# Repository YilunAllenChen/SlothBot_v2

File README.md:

# SlothBot_v2.0
The SlothBot project, v2.0. Since 2020.

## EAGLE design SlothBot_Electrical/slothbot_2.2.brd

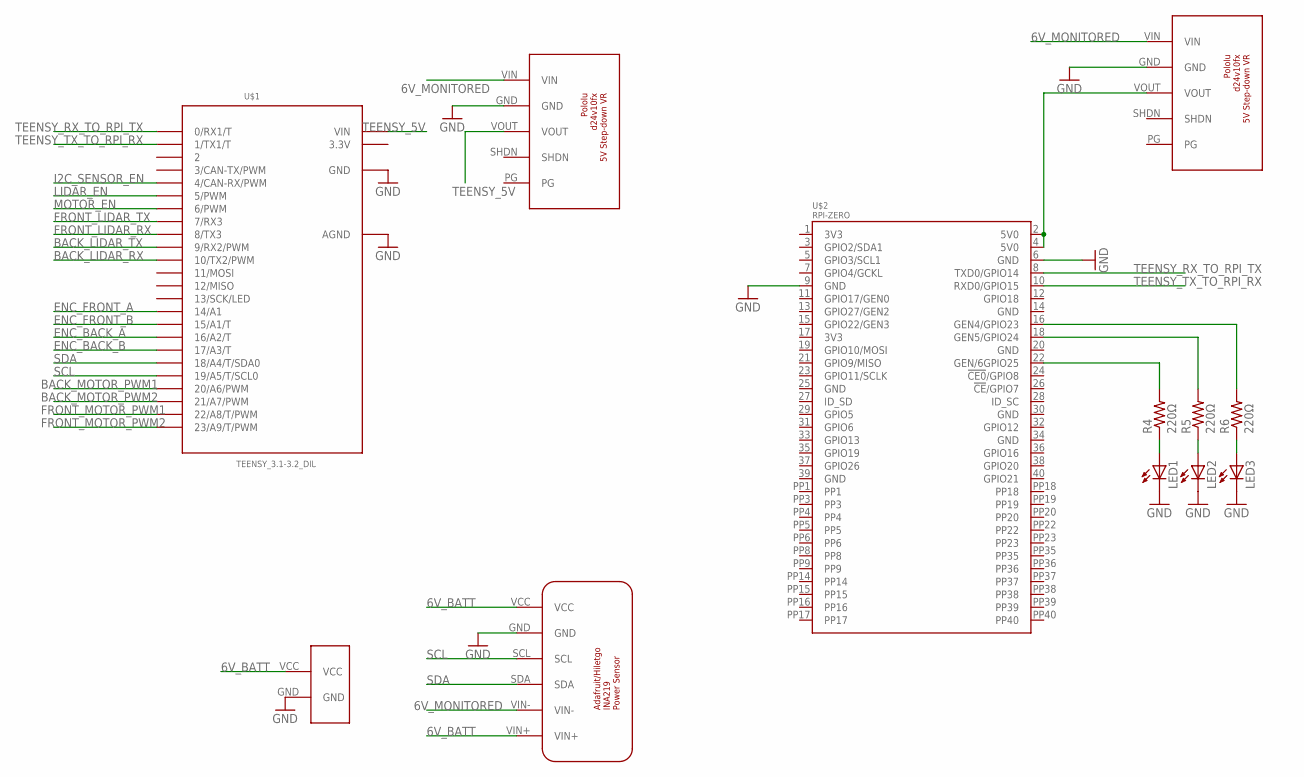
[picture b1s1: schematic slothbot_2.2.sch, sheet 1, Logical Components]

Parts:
LED1, LED2, LED3: LEDCHIPLED_0603; CHIPLED_0603
R4, R5, R6: 220Ω; R3216
U$1: TEENSY_3.1-3.2_DIL; TEENSY_3.0-3.2&LC_DIL
U$2: RPI-ZERO; RASP_PI_ZERO_BOARD_FULL
U$12, U$13: D24V10FX
U$15: INA219
U$16: BATTERY_CONNECTOR

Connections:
3.3V: U$1.3.3V
5V0@1: U$2.2 (5V0), U$2.4 (5V0), U$13.VOUT
6V_BATT: U$15.VCC, U$15.VIN+, U$16.VCC
6V_MONITORED: U$12.VIN, U$13.VIN, U$15.VIN-; also elsewhere on the board
BACK_LIDAR_RX: U$1.10 (10/TX2/PWM); also elsewhere on the board
BACK_LIDAR_TX: U$1.9 (9/RX2/PWM); also elsewhere on the board
BACK_MOTOR_PWM1: U$1.20/A6 (20/A6/PWM); also elsewhere on the board
BACK_MOTOR_PWM2: U$1.21/A7 (21/A7/PWM); also elsewhere on the board
ENC_BACK_A: U$1.16/A2 (16/A2/T); also elsewhere on the board
ENC_BACK_B: U$1.17/A3 (17/A3/T); also elsewhere on the board
ENC_FRONT_A: U$1.14/A0 (14/A1); also elsewhere on the board
ENC_FRONT_B: U$1.15/A1 (15/A1/T); also elsewhere on the board
FRONT_LIDAR_RX: U$1.8 (8/TX3); also elsewhere on the board
FRONT_LIDAR_TX: U$1.7 (7/RX3); also elsewhere on the board
FRONT_MOTOR_PWM1: U$1.22/A8 (22/A8/T/PWM); also elsewhere on the board
FRONT_MOTOR_PWM2: U$1.23/A9 (23/A9/T/PWM); also elsewhere on the board
GND: LED1.C, LED2.C, LED3.C, U$1.AGND, U$1.GND, U$2.6 (GND), U$12.GND, U$13.GND, U$15.GND, U$16.GND; also elsewhere on the board
GND@1: U$2.9 (GND)
I2C_SENSOR_EN: U$1.4 (4/CAN-RX/PWM); also elsewhere on the board
LIDAR_EN: U$1.5 (5/PWM); also elsewhere on the board
MOTOR_EN: U$1.6 (6/PWM); also elsewhere on the board
unnamed: LED1.A, R4.1
unnamed: LED2.A, R5.1
unnamed: LED3.A, R6.1
unnamed: R6.2, U$2.16 (GEN4/GPIO23)
unnamed: R5.2, U$2.18 (GEN5/GPIO24)
unnamed: R4.2, U$2.22 (GEN/6GPIO25)
SCL: U$1.19/A5 (19/A5/T/SCL0), U$15.SCL; also elsewhere on the board
SDA: U$1.18/A4 (18/A4/T/SDA0), U$15.SDA; also elsewhere on the board
TEENSY_5V: U$1.VIN, U$12.VOUT; also elsewhere on the board
TEENSY_RX_TO_RPI_TX: U$1.0 (0/RX1/T), U$2.8 (TXD0/GPIO14)
TEENSY_TX_TO_RPI_RX: U$1.1 (1/TX1/T), U$2.10 (RXD0/GPIO15)

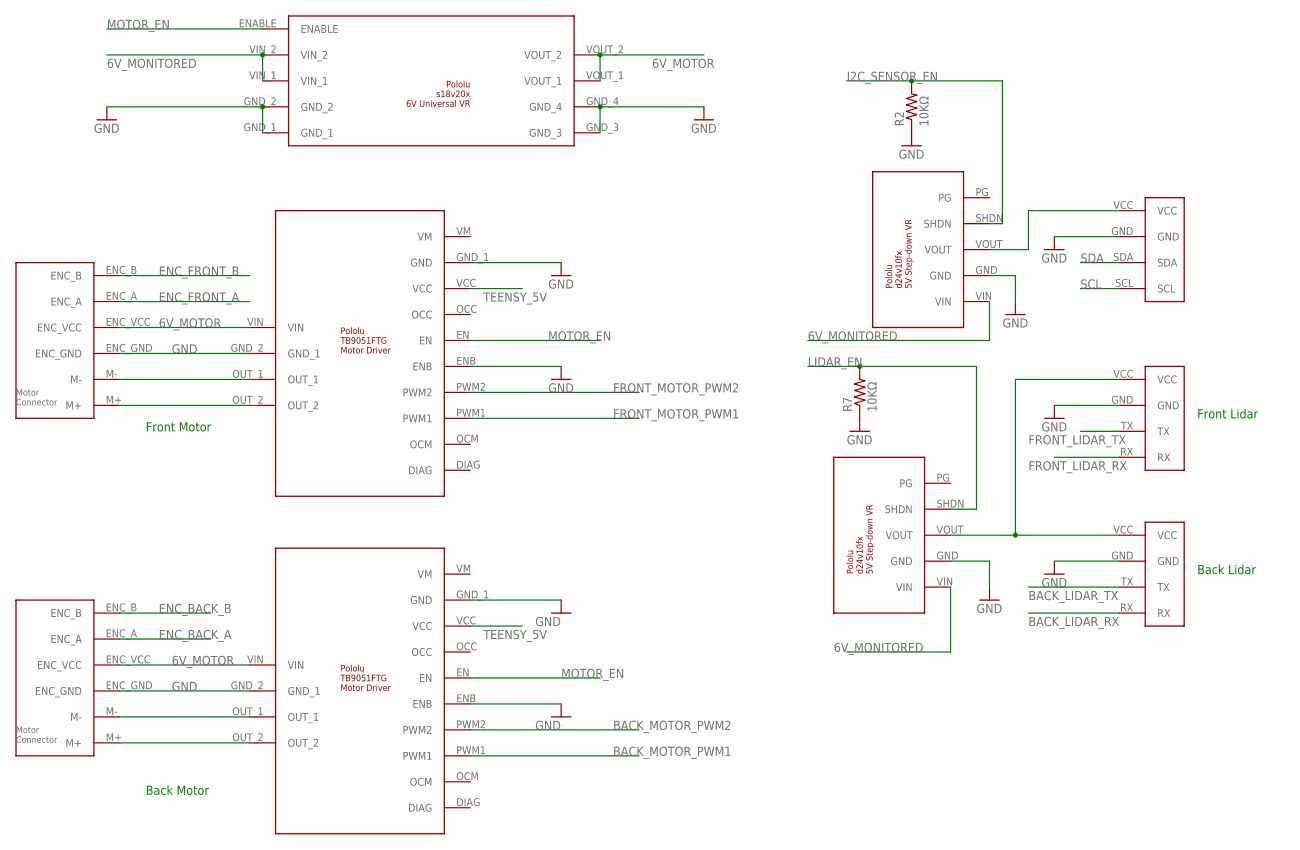
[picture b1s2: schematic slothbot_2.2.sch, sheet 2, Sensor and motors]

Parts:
R2, R7: 10KΩ; R3216
U$3, U$14: D24V10FX
U$4, U$5: MOTOR_CONNECTOR
U$6, U$7: SERIAL_CONNECTOR
U$8: I2C_CONNECTOR
U$9, U$10: TB9051FTG
U$11: S18V20X; S18V20F6

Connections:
6V_MONITORED: U$3.VIN, U$11.VIN_1, U$11.VIN_2, U$14.VIN; also elsewhere on the board
6V_MOTOR: U$4.ENC_VCC, U$5.ENC_VCC, U$9.VIN, U$10.VIN, U$11.VOUT_1, U$11.VOUT_2
BACK_LIDAR_RX: U$6.RX; also elsewhere on the board
BACK_LIDAR_TX: U$6.TX; also elsewhere on the board
BACK_MOTOR_PWM1: U$10.PWM1; also elsewhere on the board
BACK_MOTOR_PWM2: U$10.PWM2; also elsewhere on the board
ENC_BACK_A: U$5.ENC_A; also elsewhere on the board
ENC_BACK_B: U$5.ENC_B; also elsewhere on the board
ENC_FRONT_A: U$4.ENC_A; also elsewhere on the board
ENC_FRONT_B: U$4.ENC_B; also elsewhere on the board
FRONT_LIDAR_RX: U$7.RX; also elsewhere on the board
FRONT_LIDAR_TX: U$7.TX; also elsewhere on the board
FRONT_MOTOR_PWM1: U$9.PWM1; also elsewhere on the board
FRONT_MOTOR_PWM2: U$9.PWM2; also elsewhere on the board
GND: R2.1, R7.1, U$3.GND, U$4.ENC_GND, U$5.ENC_GND, U$6.GND, U$7.GND, U$8.GND, U$9.ENB, U$9.GND_1 (GND), U$9.GND_2 (GND_1), U$10.ENB, U$10.GND_1 (GND), U$10.GND_2 (GND_1), U$11.GND_1, U$11.GND_2, U$11.GND_3, U$11.GND_4, U$14.GND; also elsewhere on the board
I2C_SENSOR_EN: R2.2, U$14.SHDN; also elsewhere on the board
LIDAR_EN: R7.2, U$3.SHDN; also elsewhere on the board
MOTOR_EN: U$9.EN, U$10.EN, U$11.ENABLE; also elsewhere on the board
unnamed: U$3.VOUT, U$6.VCC, U$7.VCC
unnamed: U$4.M-, U$9.OUT_1
unnamed: U$4.M+, U$9.OUT_2
unnamed: U$5.M-, U$10.OUT_1
unnamed: U$5.M+, U$10.OUT_2
unnamed: U$8.VCC, U$14.VOUT
SCL: U$8.SCL; also elsewhere on the board
SDA: U$8.SDA; also elsewhere on the board
TEENSY_5V: U$9.VCC, U$10.VCC; also elsewhere on the board

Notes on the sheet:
Front Motor
Back Motor
Front Lidar
Back Lidar

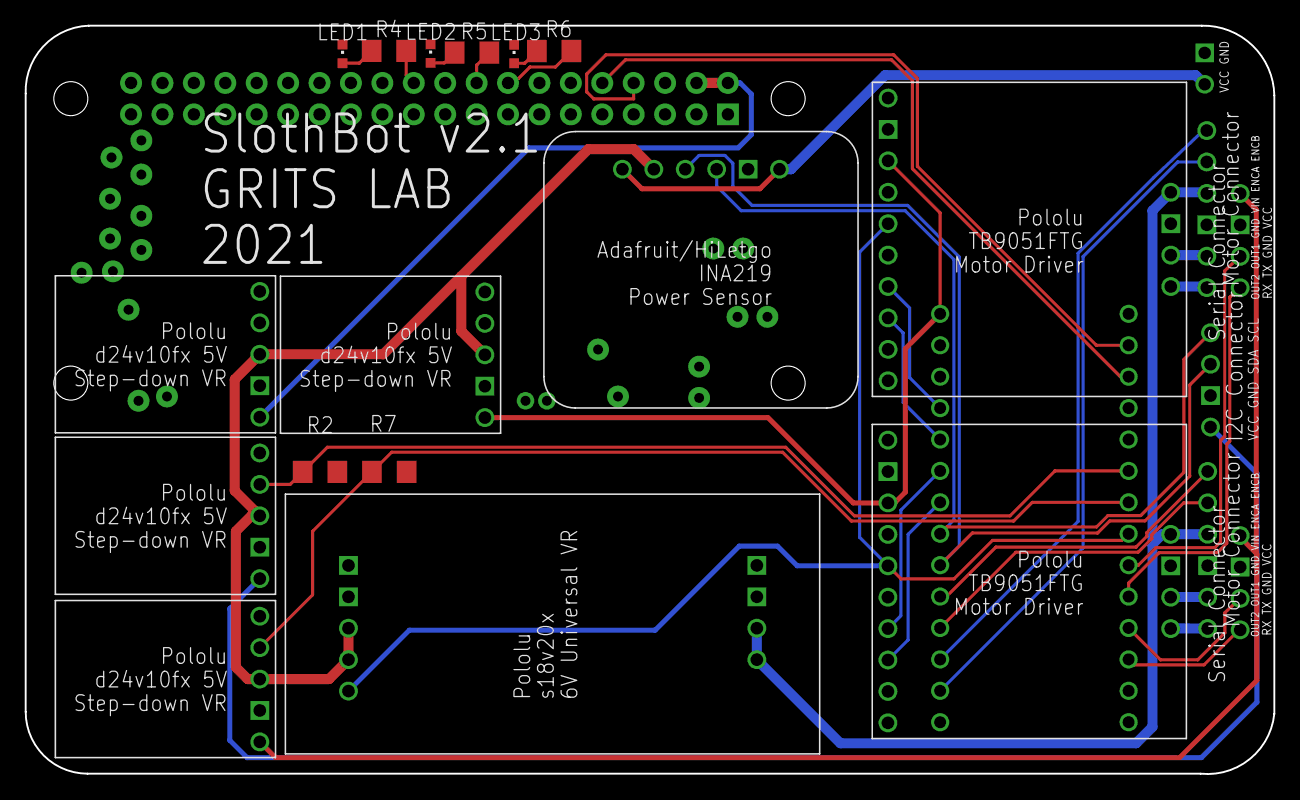
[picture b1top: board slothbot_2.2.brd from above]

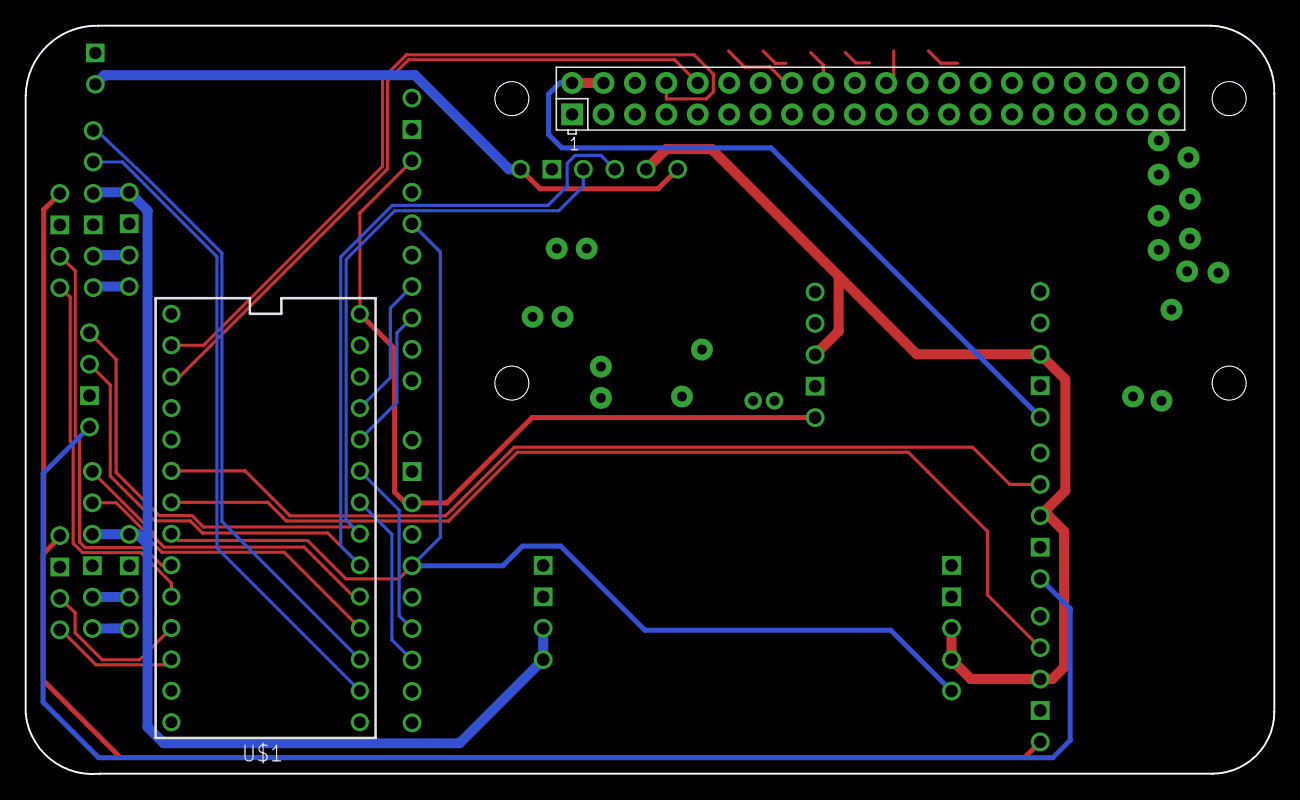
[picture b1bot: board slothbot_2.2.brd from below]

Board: 2 copper layers, 101.0 x 60.5 mm, 24 parts (2 on the bottom side), 37 nets.

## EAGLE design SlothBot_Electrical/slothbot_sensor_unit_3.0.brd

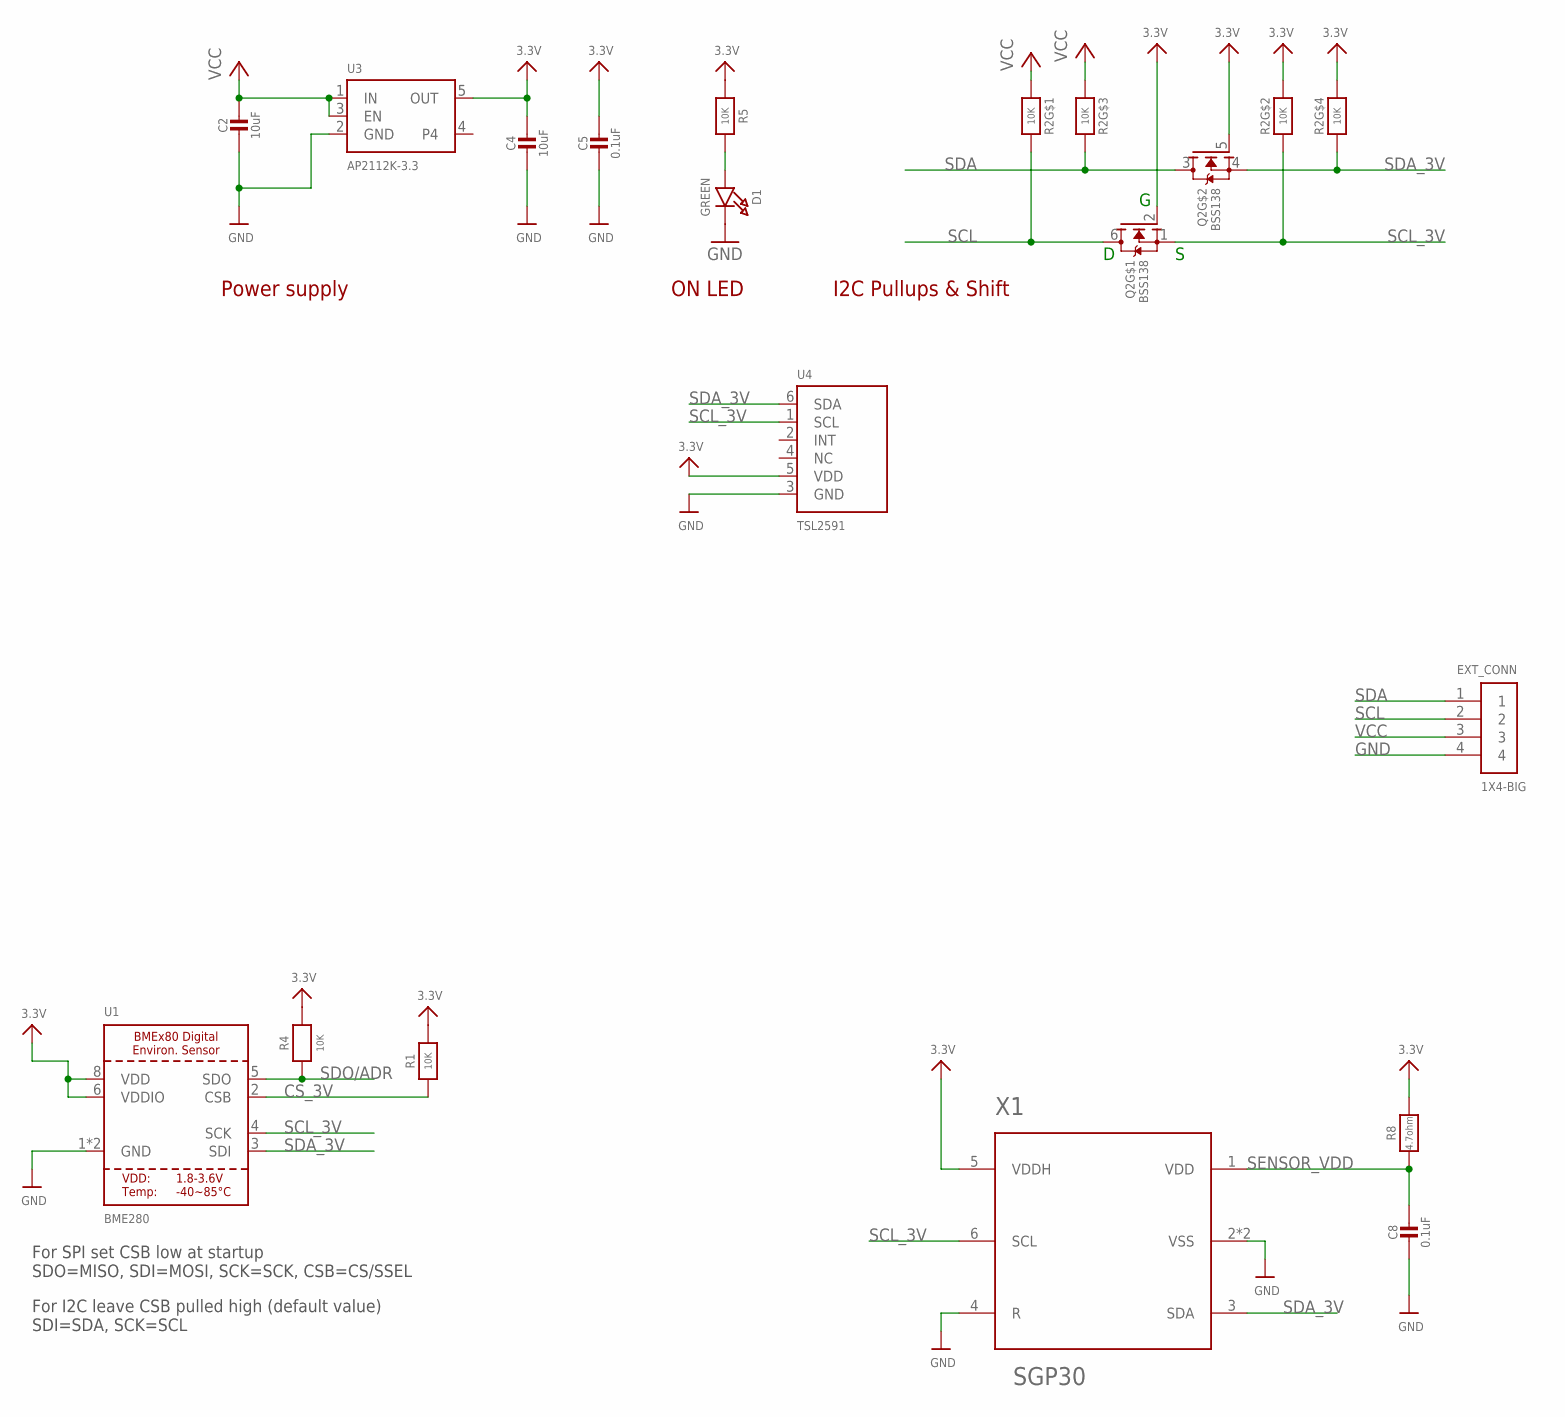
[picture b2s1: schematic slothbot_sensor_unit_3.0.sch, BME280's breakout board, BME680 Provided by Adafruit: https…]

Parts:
C2, C4: 10uF; 0805-NO
C5, C8: 0.1uF; 0603-NO
D1: GREEN; CHIPLED_0603_NOOUTLINE
EXT_CONN: 1X4-BIG; 1X04-BIG
Q2: BSS138; SOT363
R1, R4, R5: 10K; 0603-NO
R2: 10K; RESPACK_4X0603
R8: 4.7ohm; 0603-NO
U1: BME280
U3: AP2112K-3.3; SOT23-5
U4: TSL2591; DFN6_TAOS
X1: SGP30

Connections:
3.3V: C4.1, C5.1, Q2.2 (G), Q2.5 (G), R1.2, R2.2 (1), R2.4 (1), R4.2, R5.1, R8.2, U1.6 (VDDIO), U1.8 (VDD), U3.5 (OUT), U4.5 (VDD), X1.5 (VDDH)
CS_3V: R1.1, U1.2 (CSB)
GND: C2.2, C4.2, C5.2, C8.2, D1.C, EXT_CONN.4, U1.1 (GND), U1.7 (GND), U3.2 (GND), U4.3 (GND), X1.2 (VSS), X1.4 (R), X1.P$7 (VSS)
unnamed: D1.A, R5.2
SCL: EXT_CONN.2, Q2.6 (D), R2.8 (2)
SCL_3V: Q2.1 (S), R2.7 (2), U1.4 (SCK), U4.1 (SCL), X1.6 (SCL)
SDA: EXT_CONN.1, Q2.3 (D), R2.6 (2)
SDA_3V: Q2.4 (S), R2.5 (2), U1.3 (SDI), U4.6 (SDA), X1.3 (SDA)
SDO/ADR: R4.1, U1.5 (SDO)
SENSOR_VDD: C8.1, R8.1, X1.1 (VDD)
VCC: C2.1, EXT_CONN.3, R2.1, R2.3 (1), U3.1 (IN), U3.3 (EN)

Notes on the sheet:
For SPI set CSB low at startup SDO=MISO, SDI=MOSI, SCK=SCK, CSB=CS/SSEL
For I2C leave CSB pulled high (default value) SDI=SDA, SCK=SCL
I2C Pullups & Shift
ON LED
Power supply

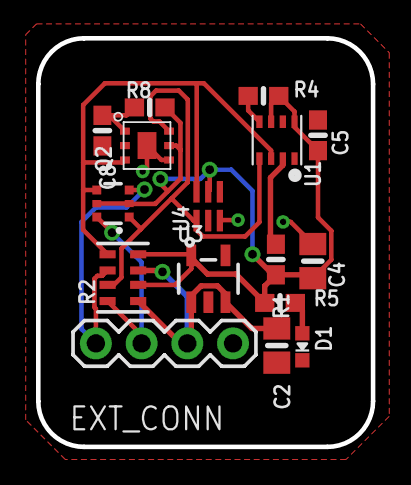
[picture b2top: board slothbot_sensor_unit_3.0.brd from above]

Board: 2 copper layers, 18.6 x 22.7 mm, 16 parts (0 on the bottom side), 11 nets.

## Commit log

2021-05-07 init commit
2021-05-07 modified setup script; teamjs.
2021-05-07 reorganized sketches
2021-05-07 setup and upload files updated; updated built website
2021-05-08 schematics/pcb added
2021-05-08 reorganized files; added pcb
2021-05-08 better documentation for firmware
2021-05-10 new pcb added
2021-05-13 updated mechanical parts
2021-05-24 updated setup script; modified led blink to comply with SlothBot v2.2; fixed errors in main.py
2021-05-24 redoing setup script
2021-05-24 redid setup script using system d
2021-05-24 global state handling
2021-05-24 updated config; main lifecycle now works on startup
2021-05-24 repo watcher now works with led
2021-05-24 fix for led blink
2021-05-24 incresed sleep time for pulling code
2021-05-24 testing autodeploy with decreased led blinking interval
2021-05-24 increasing led interval
2021-05-25 modified rc.local to reflect repo name change
2021-05-25 global async state handling
2021-05-25 asyncio debugging
2021-05-25 asyncio fix attempt
2021-05-25 testing autodeploy
2021-05-25 renamed modules
2021-05-25 testing LED autodeploy
2021-06-05 refactored cloud dashboard page
2021-06-05 removed git tracking for agent cred
2021-06-05 added cloud comm and print ip addr
2021-06-05 autorebuild for python added
2021-06-05 testing autodeploy; testing cloud comm
2021-06-05 exception handling and logging for cloud comm
2021-06-05 reduced cloud comm interval
2021-06-05 reorganized firmware files
2021-06-05 moved teensy bin around
2021-06-05 tested cloud connection
2021-06-05 added heartbeat and instruction parsing
2021-06-05 web dashbaord working
2021-06-05 command center improved; added sensor data
2021-06-05 fixed navbar
2021-06-06 home page improved
2021-06-06 desc improved
2021-06-06 rebuilt cecropia
2021-06-06 debug cloud comm
2021-06-07 updated cloud comm
2021-06-07 firmware update to prevent cloud comm from breaking
2021-06-08 retry for failed connection
2021-06-08 robot status update; robot command bank improved
2021-06-08 detached instruction handling from updating sensor data
2021-06-08 prepping for serial integration
2021-06-08 reduced repo watcher to 60 sec
2021-06-08 updated merge
2021-06-08 printing for cloud comm for debug
2021-06-08 temp removed serial code on RPI
2021-06-08 changing board mode to BOARD
2021-06-08 daded debug code
2021-06-08 stopeed reinstall package every time
2021-06-08 added cloud server
2021-06-08 using RESTful apis instead of firebase admin
2021-06-08 updated RESTful apis
2021-06-08 altered sequence for GPIO and serial intialization
2021-06-08 updated RPi firmware
2021-06-08 better handling on dashboard
2021-06-08 reduced interval of pushing updates; removed pushing random data
2021-06-08 better error handling updating data
2021-06-08 removed ip addr update
2021-06-08 changed serial port
2021-06-08 failure reading
2021-06-08 manual update
2021-06-08 added manual update
2021-06-08 temp removed read data button
2021-06-08 uploading serial comm code to teensy
2021-06-10 improved ip address reporting
2021-06-10 better heartbeat timestamping
2021-06-10 added dashboard page
2021-06-10 dashbaord page
2021-06-10 changing sequence of updating instruction queue
2021-06-10 changed sequence of sending data
2021-06-10 using per stage update instead of multiple updates
2021-06-11 updated firmware to execute instructions every 10 s
2021-06-11 added timeout for post
2021-06-11 using geolocation api instead
2021-06-11 now reports cpu usage
2021-06-11 testing grouping
2021-06-11 better refreshing & data view selection
2021-06-12 team page updated
2021-06-12 prevent rpi to override sent instruction while pulling for instruction
